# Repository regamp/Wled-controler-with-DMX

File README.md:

# WLED Controller with DMX Input

ESP32‑S3 based WLED controller with DMX512 input, fused LED outputs, and a built‑in level shifter – designed for 12V WS2815 LED strips.

## Features

- **MCU**: ESP32‑S3 (WiFi & BLE)
- **DMX512 input** via MAX485
- **4 addressable LED channels**  
  - Each with a 3.3V → 5V level shifter
  - Designed for 12V WS2815 strips (work with others ws281x)
- **4 fuses** – 5A per channel
- **Power supply**  
  - 9-24V DC input  
  - XL1509 buck converter (12V → 5V) for logic

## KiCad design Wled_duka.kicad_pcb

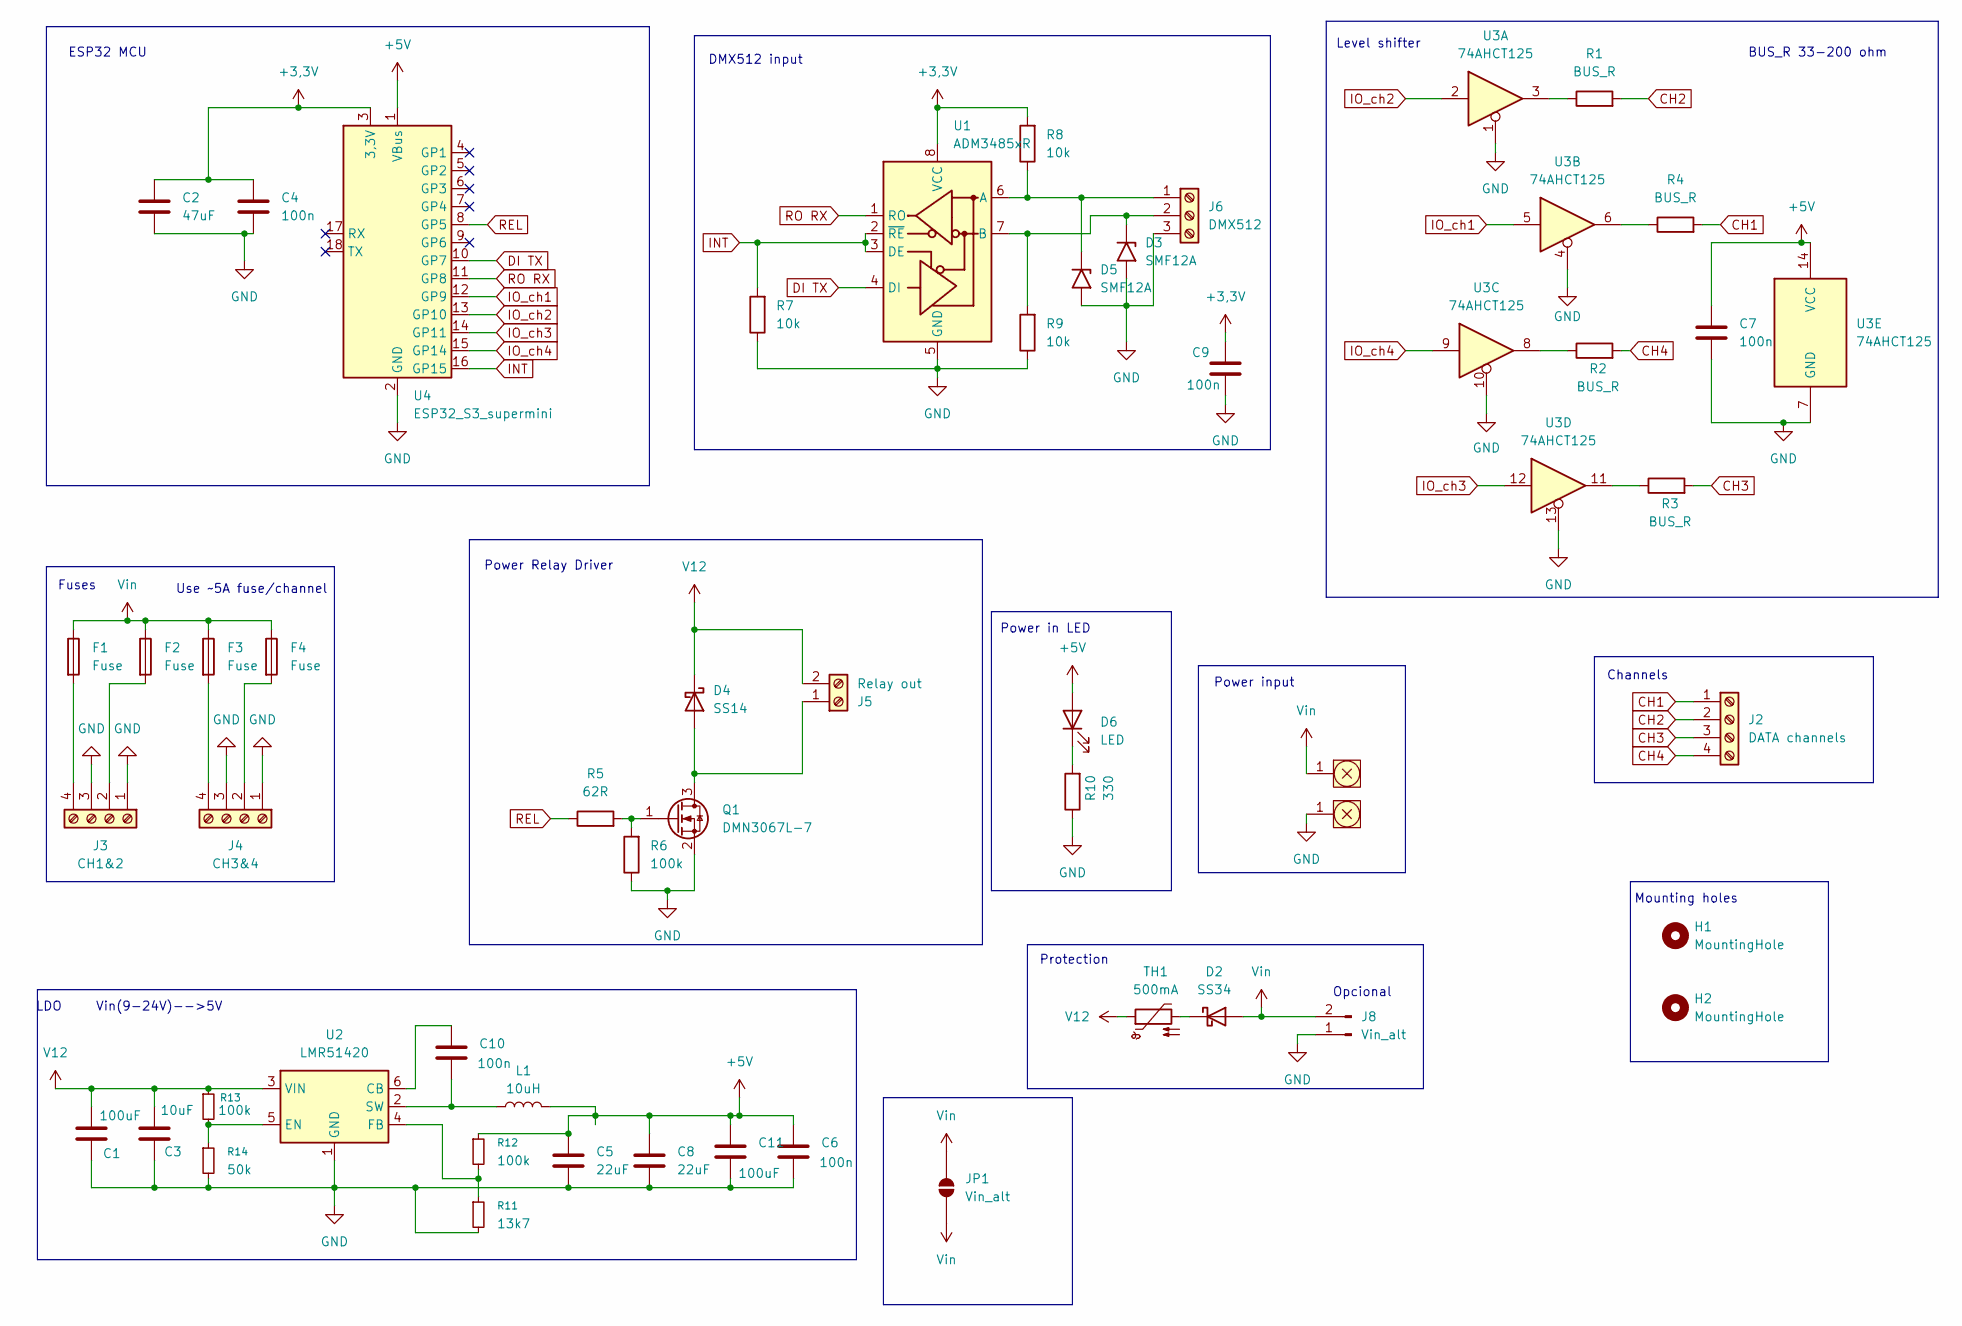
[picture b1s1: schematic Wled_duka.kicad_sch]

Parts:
C1, C11: 100uF; C_Radial_D5.0mm_H11.0mm_P2.00mm; Mouser Part Number EEU-FR1C101B
C2: 47uF; C_Radial_D5.0mm_H7.0mm_P2.00mm; Mouser Part Number 667-EEU-FR1C101B
C3: 10uF; C_1206_3216Metric_Pad1.33x1.80mm_HandSolder; Mouser Part Number 603-CC1206KKX7GBB106
C4, C6, C7, C9, C10: 100n; C_0805_2012Metric_Pad1.18x1.45mm_HandSolder; Mouser Part Number 603-AC0805KKX7R9BB10
C5, C8: 22uF; C_1210_3225Metric_Pad1.33x2.70mm_HandSolder; Mouser Part Number 603-CC121KKX7R8BB226
D2: SS34; D_SMA_Handsoldering; Mouser Part Number 821-SS34ALH
D3, D5: SMF12A; D_SMF; Mouser Part Number 576-SMF12A
D4: SS14; D_SMA; Mouser Part Number 821-SS14MH
D6: LED; LED_0805_2012Metric_Pad1.15x1.40mm_HandSolder; Mouser Part Number 859-LTST-C170KGKT
F1, F2, F3, F4: Fuse; 35222; Mouser Part Number 534-3522-2
H1, H2: MountingHole; MountingHole_5.3mm_M5_Pad
J1, J7: 7775-2; Keystone_77752; Mouser Part Number 534-7775
J2: DATA channels; TerminalBlock_Degson_DG250-3.5-04P_1x04_P3.50mm_45Degree; Mouser Part Number 490-TBL002A3504GY2GY
J3: CH1&2; TerminalBlock_Ningbo-Kagnex_HB9500_1x04_P9.5mm; Mouser Part Number 523-YK4410400000G
J4: CH3&4; TerminalBlock_Ningbo-Kagnex_HB9500_1x04_P9.5mm; Mouser Part Number 523-YK4410400000G
J5: Relay out; TerminalBlock_Phoenix_PT-1,5-2-3.5-H_1x02_P3.50mm_Horizontal; Mouser Part Number 179-TB0011-350-02GR
J6: DMX512; TerminalBlock_Phoenix_PT-1,5-3-3.5-H_1x03_P3.50mm_Horizontal; Mouser Part Number 179-TB0011-350-03GR
J8: Vin_alt; PinHeader_1x02_P2.54mm_Vertical
JP1: Vin_alt; SolderJumper-2_P1.3mm_Open_RoundedPad1.0x1.5mm
L1: 10uH; L_Bourns_SRN6045TA; Mouser Part Number 652-SRN4018-100M
Q1: DMN3067L-7; SOT-23; Mouser Part Number 621-DMN3067LW7
R1, R2, R3, R4: BUS_R; R_0805_2012Metric_Pad1.20x1.40mm_HandSolder; Mouser Part Number 603-AC0805FR-7W62RL
R5: 62R; R_0805_2012Metric_Pad1.20x1.40mm_HandSolder; Mouser Part Number 603-AC0805FR-7W62RL
R6: 100k; R_0805_2012Metric_Pad1.20x1.40mm_HandSolder; Mouser Part Number 603-AC0805FR-07100KL
R7, R8, R9: 10k; R_0805_2012Metric_Pad1.20x1.40mm_HandSolder; Mouser Part Number 603-AC0805FR-1010KL
R10: 330; R_0805_2012Metric_Pad1.20x1.40mm_HandSolder; Mouser Part Number 603-AC0805FR-07330RL
R11: 13k7; R_0805_2012Metric_Pad1.20x1.40mm_HandSolder
R12, R13: 100k; R_0805_2012Metric_Pad1.20x1.40mm_HandSolder
R14: 50k; R_0805_2012Metric_Pad1.20x1.40mm_HandSolder
TH1: 500mA; R_1206_3216Metric_Pad1.30x1.75mm_HandSolder; Mouser Part Number MF-NSMF020-2
U1: ADM3485xR; SOIC-8_3.9x4.9mm_P1.27mm; Mouser Part Number 584-ADM3485EARZ
U2: LMR51420; SOT-23-6_Handsoldering; Mouser Part Number 595-LMR51420XFDDCR
U3: 74AHCT125; SOIC-14_3.9x8.7mm_P1.27mm; Mouser Part Number 771-74HCT125D-T
U4: ESP32_S3_supermini

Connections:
+3,3V: C2.1, C4.1, C9.1, R8.2, U1.8 (VCC), U4.3 (3,3V)
+5V: C5.1, C6.2, C7.1, C8.1, C11.1, D6.2 (A), L1.2, R12.1, U3.14 (VCC), U4.1 (VBus)
CH1: J2.1, R4.2
CH2: J2.2, R1.2
CH3: J2.3, R3.2
CH4: J2.4, R2.2
DI TX: U1.4 (DI), U4.10 (GP7)
GND: C1.2, C2.2, C3.1, C4.2, C5.2, C6.1, C7.2, C8.2, C9.2, C11.2, D3.2 (A2), D5.2 (A2), J3.1, J3.3, J4.1, J4.3, J6.3, J7.1, J8.1, Q1.2 (S), R6.1, R7.1, R9.1, R10.1, R11.2, R14.2, U1.5 (GND), U2.1 (GND), U3.1, U3.4, U3.7 (GND), U3.10, U3.13, U4.2 (GND)
INT: R7.2, U1.2 (~RE), U1.3 (DE), U4.16 (GP15)
IO_ch1: U3.5, U4.12 (GP9)
IO_ch2: U3.2, U4.13 (GP10)
IO_ch3: U3.12, U4.14 (GP11)
IO_ch4: U3.9, U4.15 (GP14)
unnamed: D2.1 (K), TH1.2
unnamed: D3.1 (A1), J6.2, R9.2, U1.7 (B)
unnamed: D4.2 (A), J5.1, Q1.3 (D)
unnamed: D5.1 (A1), J6.1, R8.1, U1.6 (A)
unnamed: D6.1 (K), R10.2
unnamed: F2.2, J3.2
unnamed: F1.2, J3.4
unnamed: F4.2, J4.2
unnamed: F3.2, J4.4
unnamed: Q1.1 (G), R5.2, R6.2
unnamed: R1.1, U3.3
unnamed: R2.1, U3.8
unnamed: R3.1, U3.11
unnamed: R4.1, U3.6
unnamed: C10.2, U2.6 (CB)
unnamed: R13.2, R14.1, U2.5 (EN)
unnamed: R11.1, R12.2, U2.4 (FB)
unnamed: C10.1, L1.1, U2.2 (SW)
REL: R5.1, U4.8 (GP5)
RO RX: U1.1 (RO), U4.11 (GP8)
V12: C1.1, C3.2, D4.1 (K), J5.2, R13.1, TH1.1, U2.3 (VIN)
Vin: D2.2 (A), F1.1, F2.1, F3.1, F4.1, J1.1, J8.2, JP1.1 (A), JP1.2 (B)

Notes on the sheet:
Mounting holes
BUS_R 33-200 ohm
LDO Vin(9-24V)-->5V
Protection
Power input
Power Relay Driver
Level shifter
Fuses
Use ~5A fuse/channel
Power in LED
Opcional
ESP32 MCU
Channels
DMX512 input

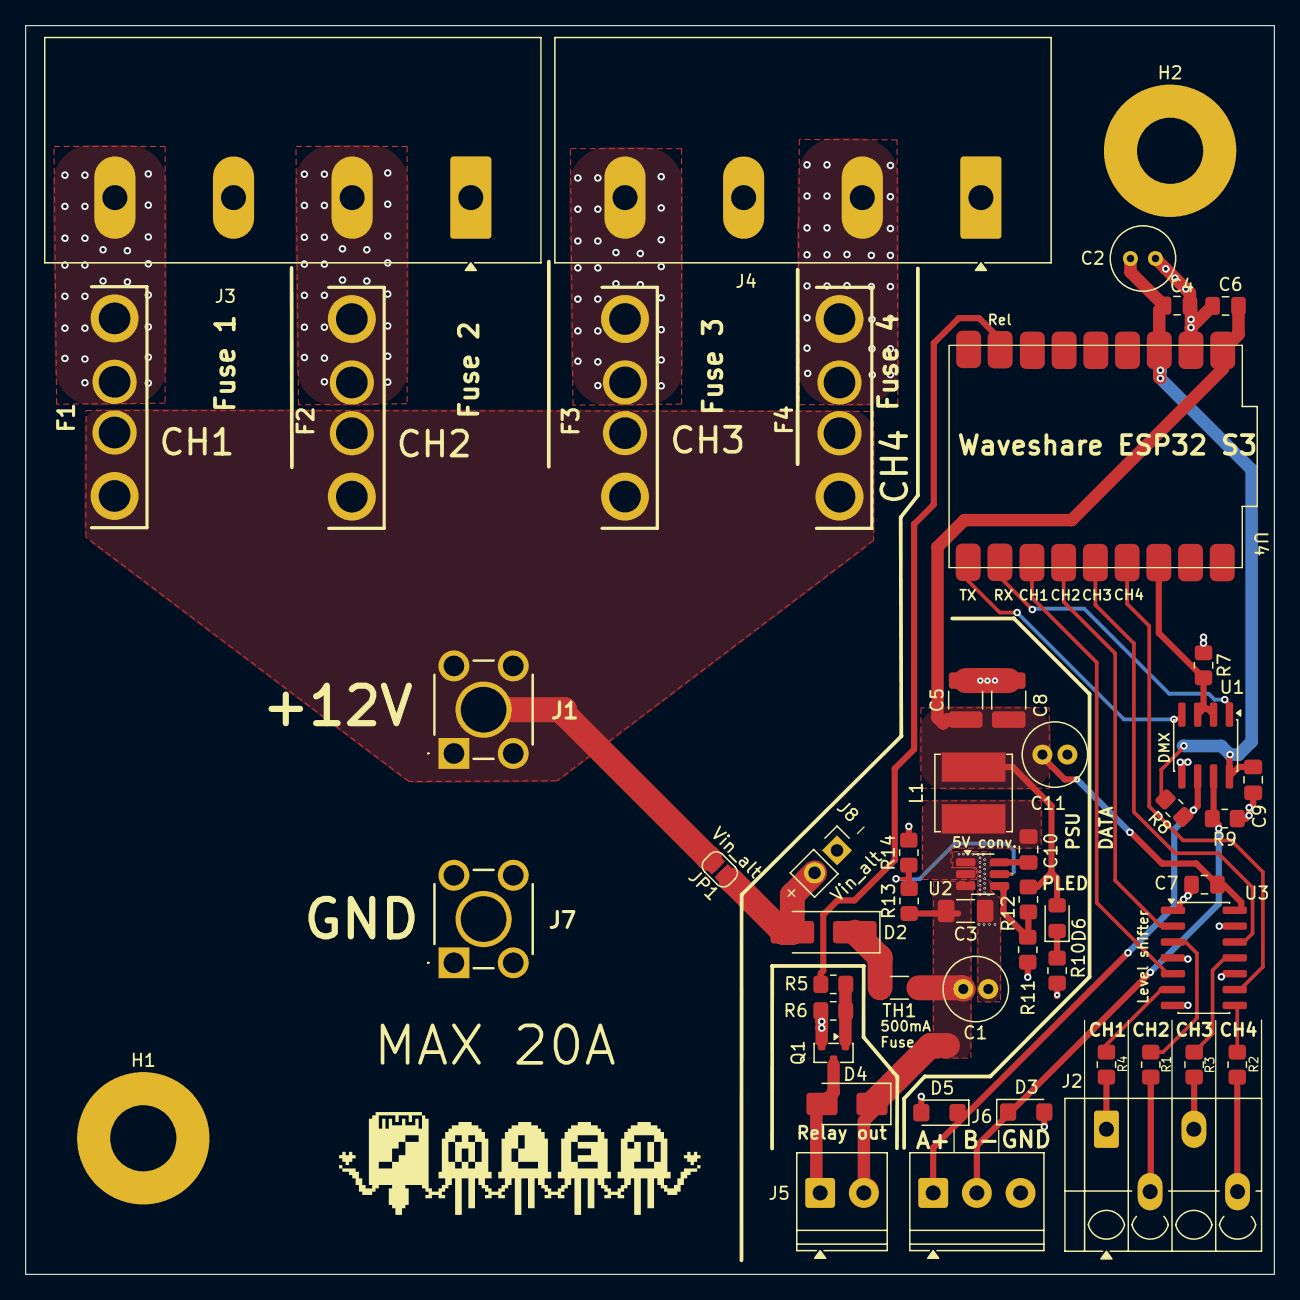
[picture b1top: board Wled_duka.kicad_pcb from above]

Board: 2 copper layers, 100.0 x 100.0 mm, 52 parts (0 on the bottom side), 35 nets.

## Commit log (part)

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2026-05-22 Wled
2026-05-22 wled v1
2026-05-22 Delete Wled_duka-backups directory
    delete
2026-05-22 Initialize README with project details
    Added project description and features for WLED controller.
2026-05-24 Update image in README for WLED Controller
    Replaced an image link with a new image for better clarity.
2026-05-24 Update power supply input voltage range in README
2026-05-25 Max485 remove --- Max3485 placed
2026-05-25 GND fix
2026-05-25 Pullup and Pulldown resistors, 3,3V for max3485
2026-06-09 Mouser.com ready components
2026-06-10 5V CAP + High current trace
2026-06-11 text fix
